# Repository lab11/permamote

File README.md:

Permamote
=========

An energy harvesting sensor mote with backing primary store and a lifetime of ≥10 years.
Permamote monitors temperature, humidity, pressure, light, light color, motion
(both PIR and with an accelerometer) and reports readings over BLE and
802.15.4/Thread.

Hardware
--------
The Permamote hardware is a small, 1 x 2.4 inch rectangular sensor board based
on the Nordic NRF52840 SoC, and the TI BQ25505 for power supply management and
energy harvesting.  Permamote also has an onboard RTC, the AB1815. The board
currently has 6 sensors:

1. Temperature and Humidity (Si7021)
2. Temperature and Pressure (MS5637)
3. Light (MAX44009)
4. Light Color (TCS34725)
5. PIR Motion (EKMB1101111)
6. Accelerometer (LIS2DW12)

The Permamote hardware is located in the [`hardware/permamote`](https://github.com/lab11/permamote/tree/master/hardware/permamote) directory, where you can find
the Eagle design files and case files.

Software
--------
The Permamote uses software located in the
[`software`](https://github.com/lab11/permamote/tree/master/software/).
directory. Follow the directions in the [nrf5x-base
Readme](https://github.com/lab11/nrf5x-base/tree/nrf52832#flash-an-application)
to get your machine set up to build and flash a Permamote.

The primary application is
[`software/apps/permamote_coap`](https://github.com/lab11/permamote/tree/master/software/apps/permamote_coap).
This application samples the
sensors and sends its data to a server running a
[coap-gateway](https://github.com/lab11/gateway/tree/thread/software/coap-gateway-mqtt)
over IP on a [Thread](https://github.com/openthread/openthread) network with a
[border router](https://github.com/openthread/borderrouter).
See the
[tutorial](https://github.com/lab11/permamote/tree/master/tutorial) to set up
your own OpenThread network.

Cloning
-------
To clone both this repository and the required submodules,
clone with the `--recurse-submodules` option:

```
git clone --recurse-submodules git@github.com:lab11/permamote.git
```

Otherwise, you can initialize the submodule and keep submodules up to
date by doing

```
git submodule update --init --recursive
```

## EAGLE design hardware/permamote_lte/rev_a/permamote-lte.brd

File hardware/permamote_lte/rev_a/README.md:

# Notes

## UFL LTE Antenna

Using this one: [Taoglas Limited FXUB65.07.0180C](https://cdn.taoglas.com/datasheets/FXUB65.07.0180C.pdf)

[Digikey here](https://www.digikey.com/product-detail/en/taoglas-limited/FXUB65.07.0180C/931-1455-ND/6362793)

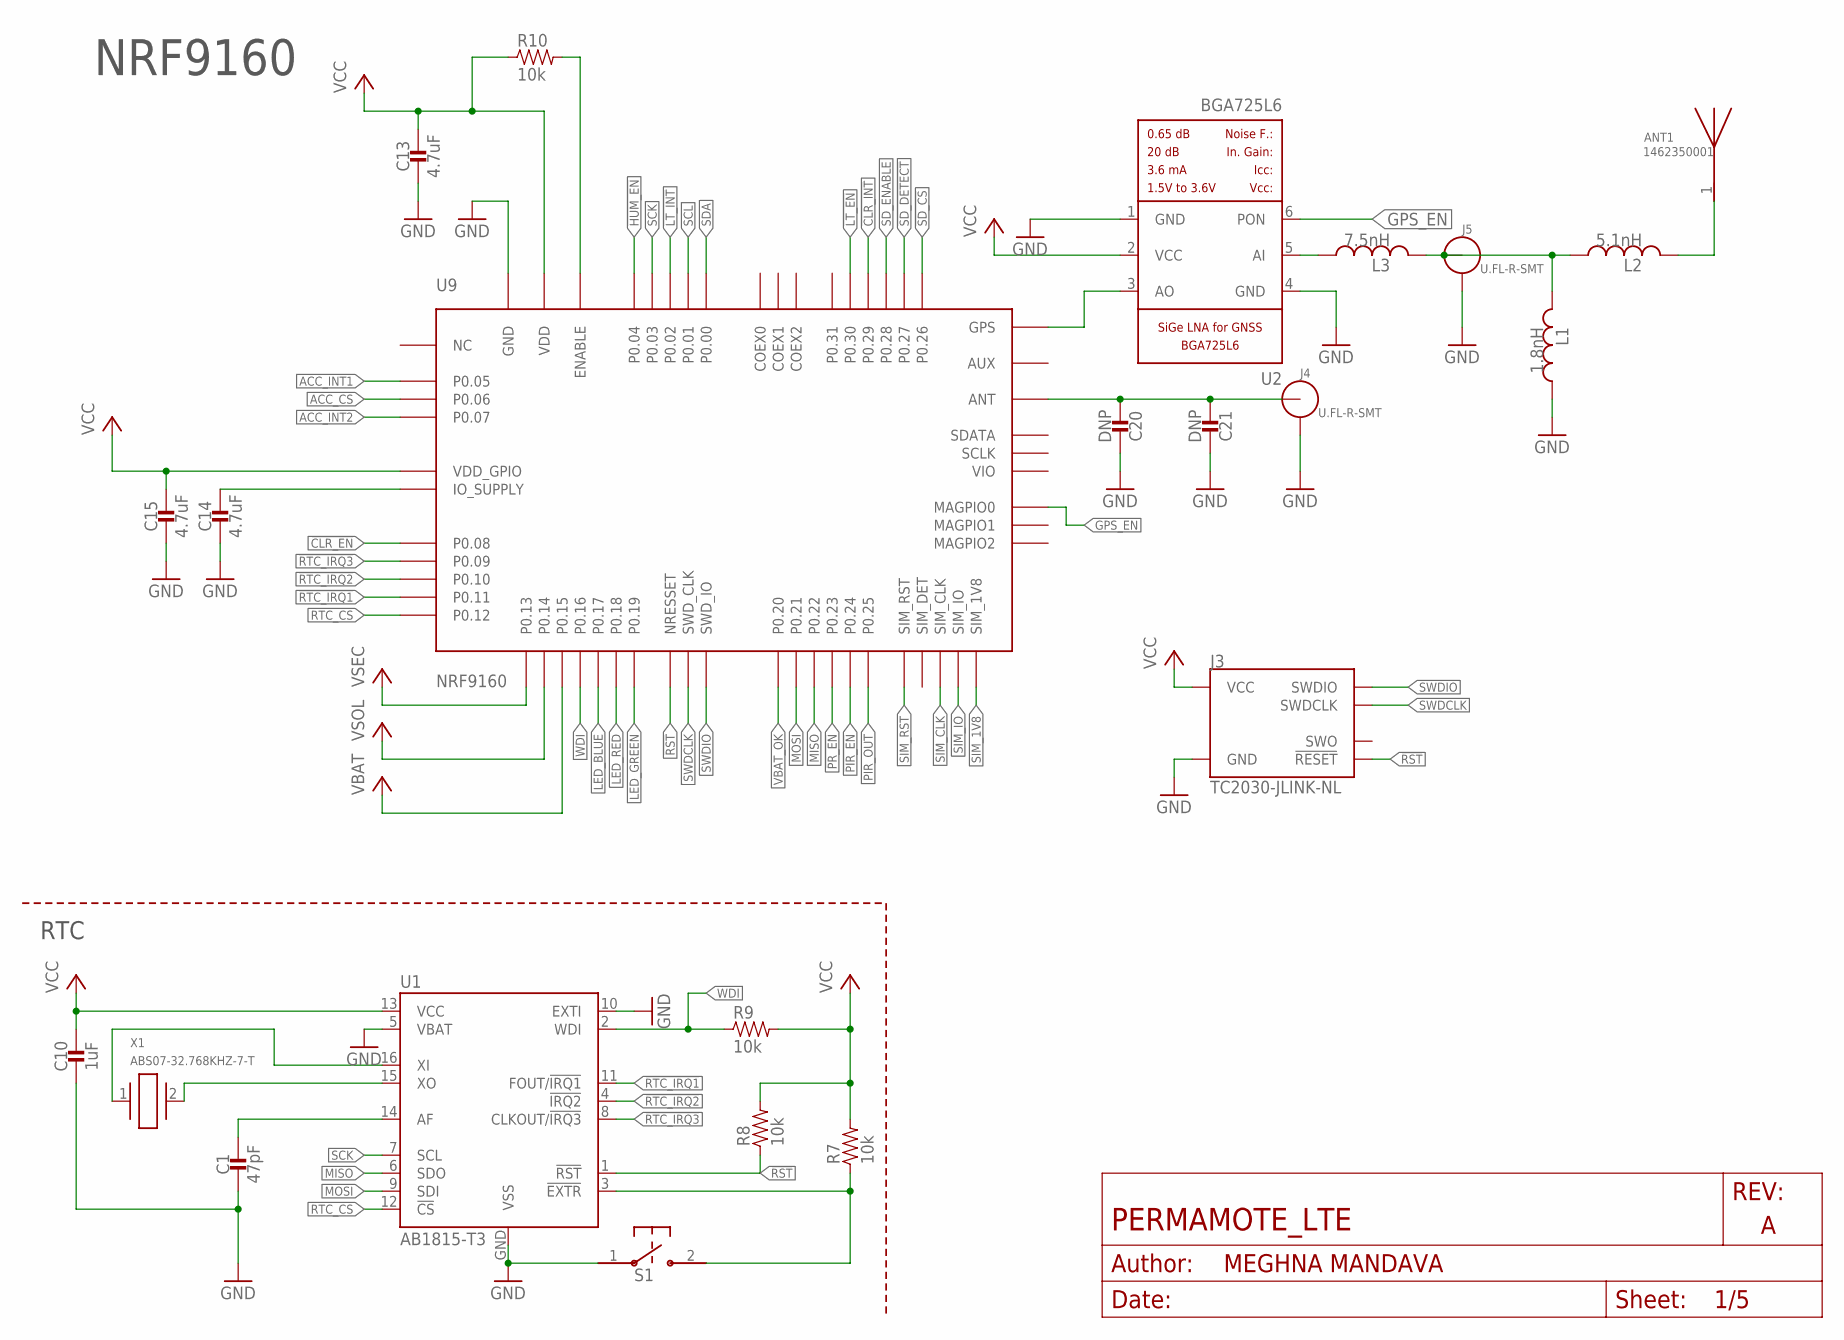
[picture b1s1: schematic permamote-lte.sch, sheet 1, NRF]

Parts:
ANT1: 1462350001; ANT_1462350001; MPN 1462350001; DIGIKEY WM15009CT-ND
C1: 47pF; 0402_CAP; MPN GRM1555C1H470JA01D; DIGIKEY 490-5942-1-ND
C10: 1uF; 0402_CAP; MPN GRM155R70G105KA12D; DIGIKEY 490-7195-1-ND
C13, C14, C15: 4.7uF; 0402_CAP; MPN C1005X5R0J475K050BC; DIGIKEY 445-5947-1-ND
C20, C21: DNP; 0402_CAP
J3: TC2030-JLINK-NL; TC2030-IDC-NL
J4, J5: U.FL-R-SMT; U.FL_SMT
L1: 1.8nH; 0402_CAP; MPN LQG15HS1N8S02D; DIGIKEY 490-2613-1-ND
L2: 5.1nH; 0402_CAP; MPN LQG15HN5N1S02D; DIGIKEY 490-6564-1-ND
L3: 7.5nH; 0402_CAP; MPN LQG15HN7N5J02D; DIGIKEY 490-6565-1-ND
R7, R8, R9, R10: 10k; 0402_RES; MPN RC0402JR-0710KL; DIGIKEY 311-10KJRCT-ND
S1: B3U-1000P
U1: AB1815-T3; QFN-16-3MM
U2: BGA725L6; LNA-TSLP-6-2-ORIG; MPN BGA725L6E6327FTSA1; DIGIKEY BGA725L6E6327FTSA1CT-ND
U9: NRF9160; MPN NRF9160-SICA-R7; DIGIKEY 1490-1076-1-ND
X1: ABS07-32.768KHZ-7-T; 2-SMD

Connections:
!CLR_EN: U9.P0.08; also elsewhere on the board
!CLR_INT: U9.P0.29; also elsewhere on the board
!HUM_EN: U9.P0.04; also elsewhere on the board
!LT_EN: U9.P0.30; also elsewhere on the board
!LT_INT: U9.P0.02; also elsewhere on the board
!PIR_EN: U9.P0.24; also elsewhere on the board
!PR_EN: U9.P0.23; also elsewhere on the board
!RST: J3.3 (!RESET), R8.1, U1.1 (!RST), U9.NRESET (NRESSET); also elsewhere on the board
!RTC_EXTR: R7.1, S1.2, U1.3 (!EXTR)
!RTC_IRQ1: U1.11 (FOUT/!IRQ1), U9.P0.11; also elsewhere on the board
!RTC_IRQ2: U1.4 (!IRQ2), U9.P0.10; also elsewhere on the board
!RTC_IRQ3: U1.8 (CLKOUT/!IRQ3), U9.P0.09; also elsewhere on the board
!SD_CS: U9.P0.26; also elsewhere on the board
!SD_DETECT: U9.P0.27; also elsewhere on the board
ACC_CS: U9.P0.06; also elsewhere on the board
ACC_INT1: U9.P0.05; also elsewhere on the board
ACC_INT2: U9.P0.07; also elsewhere on the board
GND: C1.2, C10.2, C13.2, C14.2, C15.2, C20.1, C21.1, J3.5 (GND), J4.GND1, J4.GND2, J5.GND1, J5.GND2, L1.1, S1.1, U1.5 (VBAT), U1.10 (EXTI), U1.GND (VSS), U2.1 (GND), U2.4 (GND), U9.GND@1 (GND), U9.GND@2 (GND), U9.GND@3 (GND), U9.GND@4 (GND), U9.GND@5 (GND), U9.GND@6 (GND), U9.GND@7 (GND), U9.GND@8 (GND), U9.GND@9 (GND), U9.GND@10 (GND), U9.GND@11 (GND), U9.GND@12 (GND), U9.GND@13 (GND), U9.GND@14 (GND), U9.GND@15 (GND), U9.GND@16 (GND), U9.GND@17 (GND), U9.GND@18 (GND), U9.GND@19 (GND), U9.GND@20 (GND), U9.GND@21 (GND), U9.GND@22 (GND), U9.GND@23 (GND), U9.GND@24 (GND), U9.GND@25 (GND), U9.GND@26 (GND), U9.GND@27 (GND), U9.GND@28 (GND), U9.GND@29 (GND), U9.GND@30 (GND), U9.GND@31 (GND), U9.GND@32 (GND), U9.GND@33 (GND), U9.GND@34 (GND), U9.GND@35 (GND), U9.GND_SHIELD@1 (GND), U9.GND_SHIELD@2 (GND), U9.GND_SHIELD@3 (GND), U9.GND_SHIELD@4 (GND), U9.GND_SHIELD@5 (GND), U9.GND_SHIELD@6 (GND), U9.GND_SHIELD@7 (GND), U9.GND_SHIELD@8 (GND), U9.GND_SHIELD@9 (GND), U9.GND_SHIELD@10 (GND), U9.GND_SHIELD@11 (GND), U9.GND_SHIELD@12 (GND), U9.GND_SHIELD@13 (GND), U9.GND_SHIELD@14 (GND), U9.GND_SHIELD@15 (GND), U9.GND_SHIELD@16 (GND), U9.GND_SHIELD@17 (GND), U9.GND_SHIELD@18 (GND), U9.GND_SHIELD@19 (GND), U9.GND_SHIELD@20 (GND), U9.GND_SHIELD@21 (GND), U9.GND_SHIELD@22 (GND), U9.GND_SHIELD@23 (GND), U9.GND_SHIELD@24 (GND), U9.GND_SHIELD@25 (GND), U9.GND_SHIELD@26 (GND), U9.GND_SHIELD@27 (GND), U9.GND_SHIELD@28 (GND), U9.GND_SHIELD@29 (GND), U9.GND_SHIELD@30 (GND), U9.GND_SHIELD@31 (GND), U9.GND_SHIELD@32 (GND), U9.GND_SHIELD@33 (GND), U9.GND_SHIELD@34 (GND); also elsewhere on the board
GPS_EN: U2.6 (PON), U9.MAGPIO0
LED_BLUE: U9.P0.17; also elsewhere on the board
LED_GREEN: U9.P0.19; also elsewhere on the board
LED_RED: U9.P0.18; also elsewhere on the board
MISO: U1.6 (SDO), U9.P0.22; also elsewhere on the board
MOSI: U1.9 (SDI), U9.P0.21; also elsewhere on the board
unnamed: U2.3 (AO), U9.GPS
unnamed: L3.1, U2.5 (AI)
unnamed: J5.SIG (ANT), L1.2, L2.1, L3.2
unnamed: ANT1.1, L2.2
unnamed: C20.2, C21.2, J4.SIG (ANT), U9.ANT
unnamed: C1.1, U1.14 (AF)
unnamed: R10.2, U9.ENABLE
unnamed: C14.1, U9.IO_SUPPLY
unnamed: U1.15 (XO), X1.2
unnamed: U1.16 (XI), X1.1
PIR_OUT: U9.P0.25; also elsewhere on the board
RTC_CS: U1.12 (!CS), U9.P0.12; also elsewhere on the board
SCK: U1.7 (SCL), U9.P0.03; also elsewhere on the board
SCL: U9.P0.01; also elsewhere on the board
SDA: U9.P0.00; also elsewhere on the board
SD_ENABLE: U9.P0.28; also elsewhere on the board
SIM_1V8: U9.SIM_1V8; also elsewhere on the board
SIM_CLK: U9.SIM_CLK; also elsewhere on the board
SIM_IO: U9.SIM_IO; also elsewhere on the board
SIM_RST: U9.SIM_RST; also elsewhere on the board
SWDCLK: J3.4 (SWDCLK), U9.SWDCLK (SWD_CLK)
SWDIO: J3.2 (SWDIO), U9.SWDIO (SWD_IO)
VBAT: U9.P0.15; also elsewhere on the board
VBAT_OK: U9.P0.20; also elsewhere on the board
VCC: C10.1, C13.1, C15.1, J3.1 (VCC), R7.2, R8.2, R9.2, R10.1, U1.13 (VCC), U2.2 (VCC), U9.VDD@1 (VDD), U9.VDD@2 (VDD), U9.VDD_GPIO; also elsewhere on the board
VSEC: U9.P0.13; also elsewhere on the board
VSOL: U9.P0.14; also elsewhere on the board
WDI: R9.1, U1.2 (WDI), U9.P0.16; also elsewhere on the board

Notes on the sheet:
NRF9160
RTC

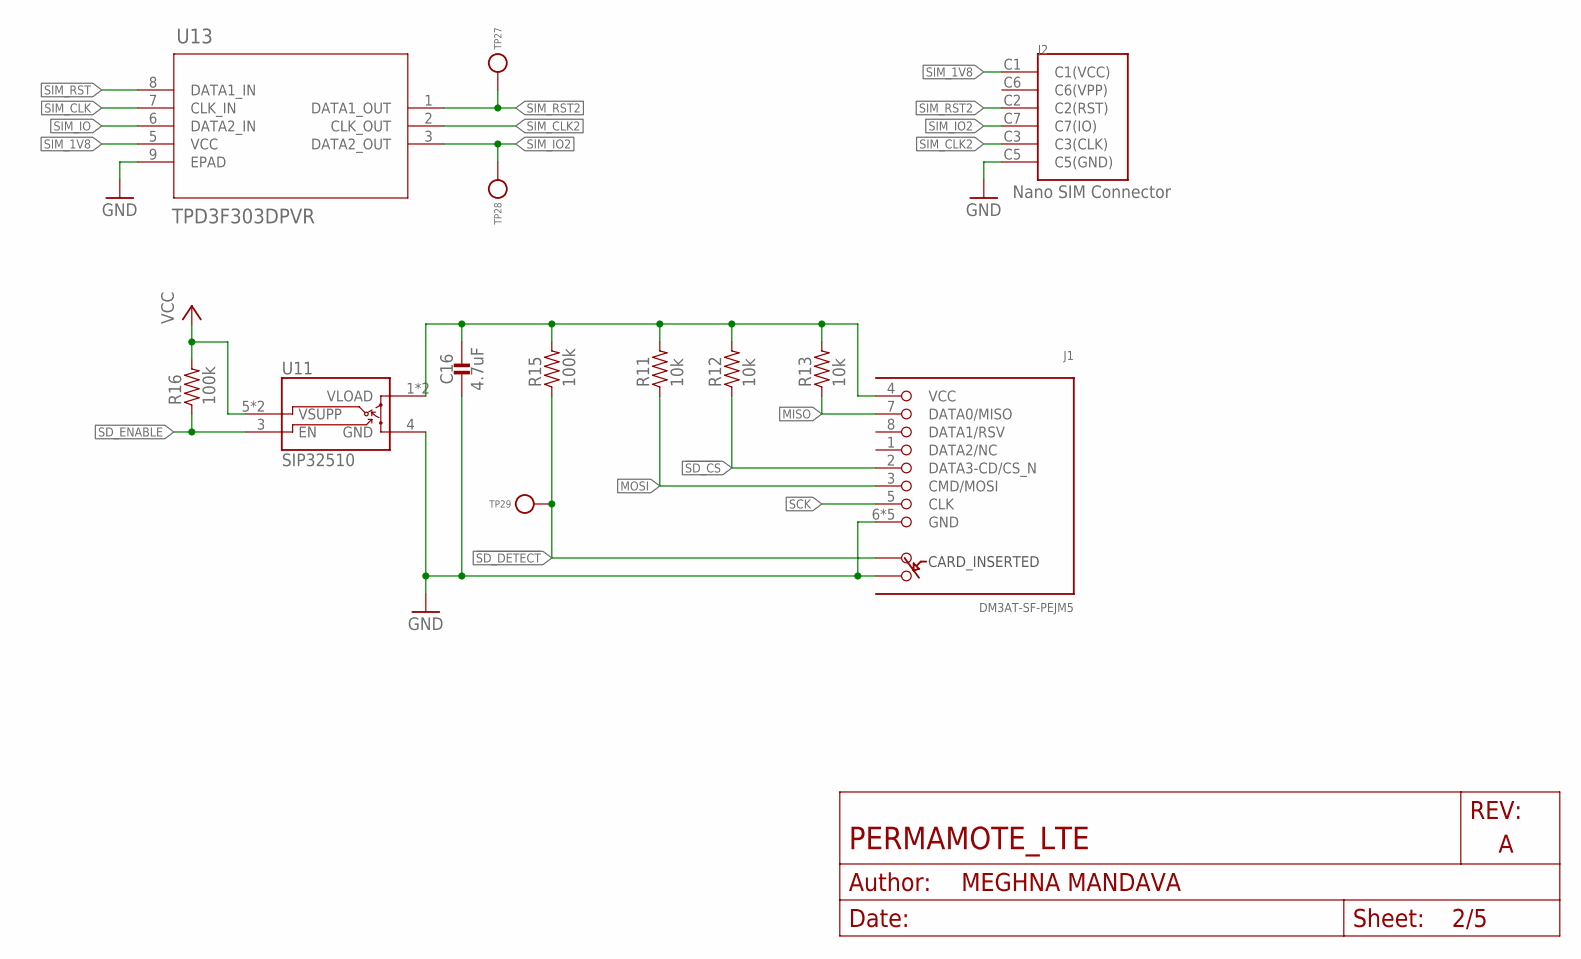
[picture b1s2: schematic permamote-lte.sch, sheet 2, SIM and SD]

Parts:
C16: 4.7uF; 0402_CAP; MPN C1005X5R0J475K050BC; DIGIKEY 445-5947-1-ND
J1: DM3AT-SF-PEJM5
J2: NANO_SIM; WURTH_NANO_SIM
R11, R12, R13: 10k; 0402_RES; MPN RC0402JR-0710KL; DIGIKEY 311-10KJRCT-ND
R15, R16: 100k; 0402_RES; MPN CRCW0402100KFKEDHP; DIGIKEY 541-100KYCT-ND
TP27, TP28, TP29: TEST-POINT; PAD.03X.03
U11: SIP32510; TSOT23-6
U13: TPD3F303DPVR; DPV8_1P7X0P4; MPN TPD3F303DPVR; DIGIKEY 296-28299-1-ND

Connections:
!SD_CS: J1.2 (DATA3-CD/CS_N), R12.1; also elsewhere on the board
!SD_DETECT: J1.A, R15.1, TP29.P$1; also elsewhere on the board
GND: C16.2, J1.6 (GND), J1.B, J1.MOUNT0 (GND), J1.MOUNT1 (GND), J1.MOUNT2 (GND), J1.MOUNT3 (GND), J2.C5 (C5(GND)), U11.4 (GND), U13.9 (EPAD); also elsewhere on the board
MISO: J1.7 (DATA0/MISO), R13.1; also elsewhere on the board
MOSI: J1.3 (CMD/MOSI), R11.1; also elsewhere on the board
unnamed: C16.1, J1.4 (VCC), R11.2, R12.2, R13.2, R15.2, U11.1 (VLOAD), U11.2 (VLOAD)
SCK: J1.5 (CLK); also elsewhere on the board
SD_ENABLE: R16.1, U11.3 (EN); also elsewhere on the board
SIM_1V8: J2.C1 (C1(VCC)), U13.5 (VCC); also elsewhere on the board
SIM_CLK: U13.7 (CLK_IN); also elsewhere on the board
SIM_CLK2: J2.C3 (C3(CLK)), U13.2 (CLK_OUT)
SIM_IO: U13.6 (DATA2_IN); also elsewhere on the board
SIM_IO2: J2.C7 (C7(IO)), TP28.P$1, U13.3 (DATA2_OUT)
SIM_RST: U13.8 (DATA1_IN); also elsewhere on the board
SIM_RST2: J2.C2 (C2(RST)), TP27.P$1, U13.1 (DATA1_OUT)
VCC: R16.2, U11.5 (VSUPP), U11.6 (VSUPP); also elsewhere on the board

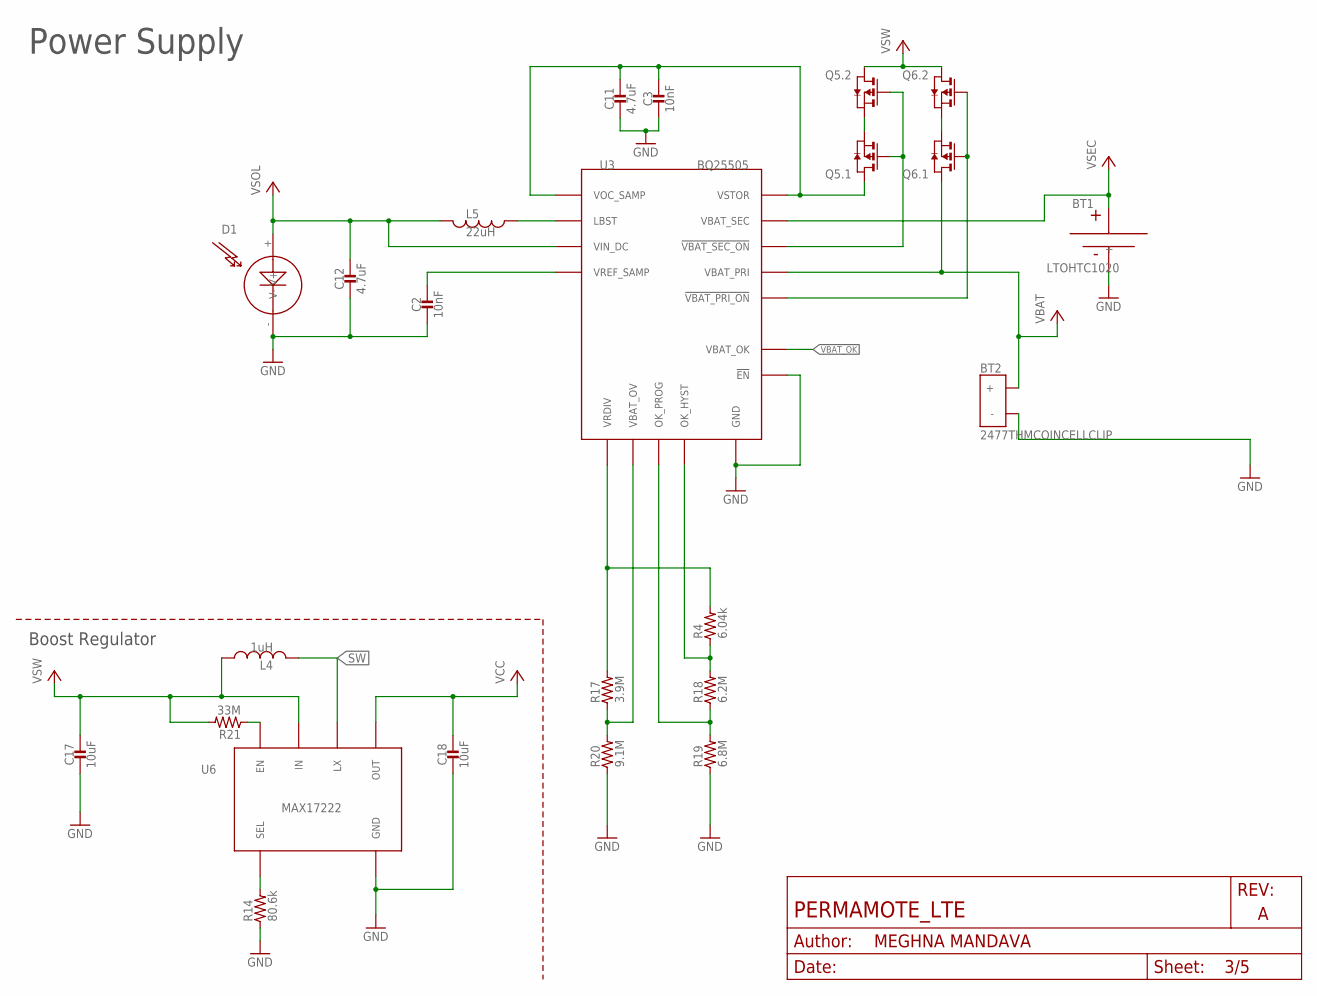
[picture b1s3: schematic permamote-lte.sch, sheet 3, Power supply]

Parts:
BT1: LTOHTC1020; 1020
BT2: 2477THMCOINCELLCLIP; 2477THMCOINCLIP
C2, C3: 10nF; 0402_CAP; MPN GRM155R71H103KA88D; DIGIKEY 490-4516-1-ND
C11, C12: 4.7uF; 0402_CAP; MPN C1005X5R0J475K050BC; DIGIKEY 445-5947-1-ND
C17, C18: 10uF; 0603_CAP; MPN GRM188R60J106ME47D; DIGIKEY 490-3896-1-ND
D1: SOLARCELLHOLES; SOLAR_HOLES
L4: 1uH; IHL-1212BZ-11; MPN IHLP1212BZER1R0M11; DIGIKEY 541-1319-1-ND
L5: 22uH; 74437324220; MPN 74437324220; DIGIKEY 732-3340-1-ND
Q5, Q6: PMDXB950UPEL; XDFN-6
R4: 6.04k; 0402_RES; MPN RC0402FR-076K04L; DIGIKEY YAG2293CT-ND
R14: 80.6k; 0603-RES; MPN RC0603FR-0780K6L; DIGIKEY 311-80.6KHRCT-ND
R17: 3.9M; 0402_RES; MPN RC0402JR-073M9L; DIGIKEY YAG3301CT-ND
R18: 6.2M; 0402_RES; MPN RC0402JR-076M2L; DIGIKEY YAG3309CT-ND
R19: 6.8M; 0402_RES; MPN RC0402JR-076M8L; DIGIKEY YAG3310CT-ND
R20: 9.1M; 0402_RES; MPN RC0402JR-079M1L; DIGIKEY YAG3322CT-ND
R21: 33M; 0603-RES; MPN HMC0603JT33M0; DIGIKEY HMC0603JT33M0CT-ND
U3: BQ25505; S-PVQFN-N20-RGR
U6: MAX17222; UDFN-6-MAXIM

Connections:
!VBAT_PRI_ON: Q6.2 (G), Q6.5 (G), U3.10 (!VBAT_PRI_ON)
!VBAT_SEC_ON: Q5.2 (G), Q5.5 (G), U3.9 (!VBAT_SEC_ON)
GND: BT1.-, BT2.GND (-), C2.2, C3.2, C11.2, C12.2, C17.2, C18.2, D1.- (V-), R14.1, R19.1, R20.1, U3.1 (GND), U3.5 (!EN), U3.6 (GND), U3.15 (GND), U3.16 (GND), U3.17 (GND), U3.PAD (GND), U6.3 (GND); also elsewhere on the board
LBST: L5.P$1 (1), U3.20 (LBST)
unnamed: R14.2, U6.4 (SEL)
unnamed: R21.1, U6.6 (EN)
unnamed: R17.1, R20.2, U3.7 (VBAT_OV)
unnamed: R4.2, R17.2, U3.8 (VRDIV)
unnamed: Q5.1 (S), Q5.4 (S)
unnamed: Q6.1 (S), Q6.4 (S)
unnamed: R18.1, R19.2, U3.12 (OK_PROG)
unnamed: R4.1, R18.2, U3.11 (OK_HYST)
SW: L4.P$2 (2), U6.2 (LX); also elsewhere on the board
VBAT: BT2.1 (+), BT2.2 (+), Q6.6 (D), U3.14 (VBAT_PRI); also elsewhere on the board
VBAT_OK: U3.13 (VBAT_OK); also elsewhere on the board
VCC: C18.1, U6.1 (OUT); also elsewhere on the board
VOC_SAMP_VSTOR: C3.1, C11.1, Q5.6 (D), U3.3 (VOC_SAMP), U3.19 (VSTOR)
VREF_SAMP: C2.1, U3.4 (VREF_SAMP)
VSEC: BT1.+, U3.18 (VBAT_SEC); also elsewhere on the board
VSOL: C12.1, D1.+ (V+), L5.P$2 (2), U3.2 (VIN_DC); also elsewhere on the board
VSW: C17.1, L4.P$1 (1), Q5.3 (D), Q6.3 (D), R21.2, U6.5 (IN)

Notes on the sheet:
Power Supply
Boost Regulator

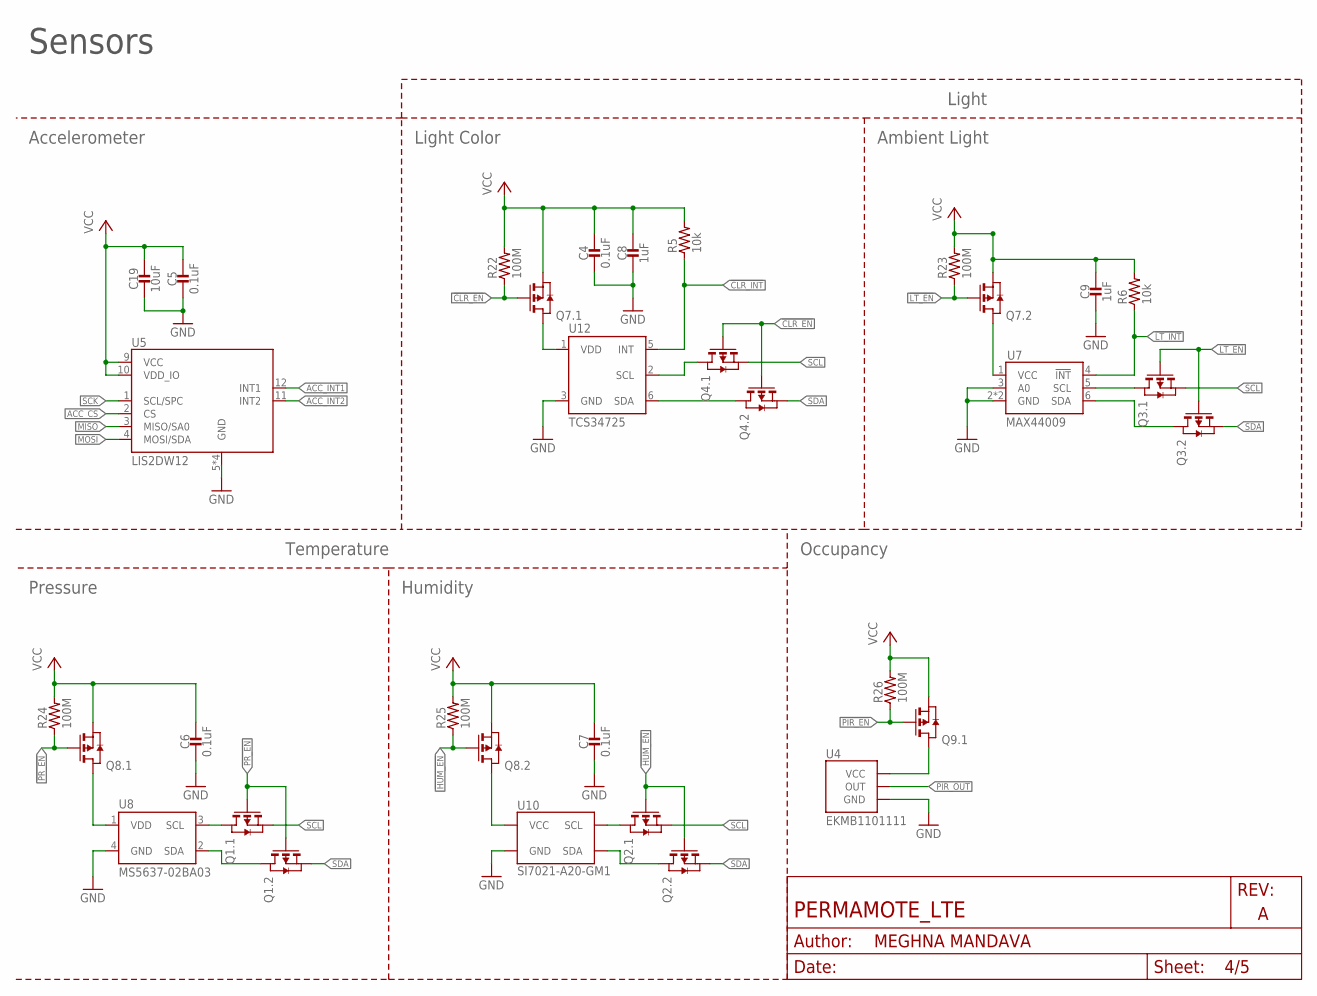
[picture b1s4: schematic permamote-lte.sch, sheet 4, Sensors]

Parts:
C4, C5, C6, C7: 0.1uF; 0402_CAP; MPN GRM155R71C104KA88J; DIGIKEY 490-6328-1-ND
C8, C9: 1uF; 0402_CAP; MPN GRM155R70G105KA12D; DIGIKEY 490-7195-1-ND
C19: 10uF; 0603_CAP; MPN GRM188R60J106ME47D; DIGIKEY 490-3896-1-ND
Q1, Q2, Q3, Q4, Q7, Q8, Q9: PMDXB950UPEL; XDFN-6
R5, R6: 10k; 0402_RES; MPN RC0402JR-0710KL; DIGIKEY 311-10KJRCT-ND
R22, R23, R24, R25, R26: 100M; 0402_RES; MPN HMC0402JT100M; DIGIKEY 541-100MAHCT-ND
U4: EKMB1101111; AMN2
U5: LIS2DW12; LGA-12
U7: MAX44009; UDFN-6-EXPOSED
U8: MS5637-02BA03; 4-SMD
U10: SI7021-A20-GM1; DFN-6/3MM; MPN SI7021-A20-GM1
U12: TCS34725; FN-6

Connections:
!CLR_EN: Q4.2 (G), Q4.5 (G), Q7.2 (G), R22.1; also elsewhere on the board
!CLR_INT: R5.1, U12.5 (INT); also elsewhere on the board
!HUM_EN: Q2.2 (G), Q2.5 (G), Q8.5 (G), R25.1; also elsewhere on the board
!LT_EN: Q3.2 (G), Q3.5 (G), Q7.5 (G), R23.1; also elsewhere on the board
!LT_INT: R6.1, U7.4 (!INT); also elsewhere on the board
!PIR_EN: Q9.2 (G), R26.1; also elsewhere on the board
!PR_EN: Q1.2 (G), Q1.5 (G), Q8.2 (G), R24.1; also elsewhere on the board
ACC_CS: U5.2 (CS); also elsewhere on the board
ACC_INT1: U5.12 (INT1); also elsewhere on the board
ACC_INT2: U5.11 (INT2); also elsewhere on the board
GND: C4.2, C5.2, C6.2, C7.2, C8.2, C9.2, C19.2, U4.GND, U5.5 (GND), U5.6 (GND), U5.7 (GND), U5.8 (GND), U7.2 (GND), U7.3 (A0), U7.EP (GND), U8.4 (GND), U10.2 (GND), U12.3 (GND); also elsewhere on the board
MISO: U5.3 (MISO/SA0); also elsewhere on the board
MOSI: U5.4 (MOSI/SDA); also elsewhere on the board
unnamed: Q7.3 (D), U7.1 (VCC)
unnamed: Q8.6 (D), U8.1 (VDD)
unnamed: Q8.3 (D), U10.5 (VCC)
unnamed: Q9.6 (D), U4.VCC
unnamed: Q7.6 (D), U12.1 (VDD)
unnamed: Q1.6 (D), U8.3 (SCL)
unnamed: Q1.3 (D), U8.2 (SDA)
unnamed: Q2.3 (D), U10.1 (SDA)
unnamed: Q2.6 (D), U10.6 (SCL)
unnamed: Q3.3 (D), U7.6 (SDA)
unnamed: Q3.6 (D), U7.5 (SCL)
unnamed: Q4.3 (D), U12.6 (SDA)
unnamed: Q4.6 (D), U12.2 (SCL)
PIR_OUT: U4.OUT; also elsewhere on the board
SCK: U5.1 (SCL/SPC); also elsewhere on the board
SCL: Q1.1 (S), Q2.1 (S), Q3.1 (S), Q4.1 (S); also elsewhere on the board
SDA: Q1.4 (S), Q2.4 (S), Q3.4 (S), Q4.4 (S); also elsewhere on the board
VCC: C4.1, C5.1, C6.1, C7.1, C8.1, C9.1, C19.1, Q7.1 (S), Q7.4 (S), Q8.1 (S), Q8.4 (S), Q9.1 (S), R5.2, R6.2, R22.2, R23.2, R24.2, R25.2, R26.2, U5.9 (VCC), U5.10 (VDD_IO); also elsewhere on the board

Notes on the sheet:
Sensors
Accelerometer
Temperature
Humidity
Pressure
Ambient Light
Light Color
Light
Occupancy

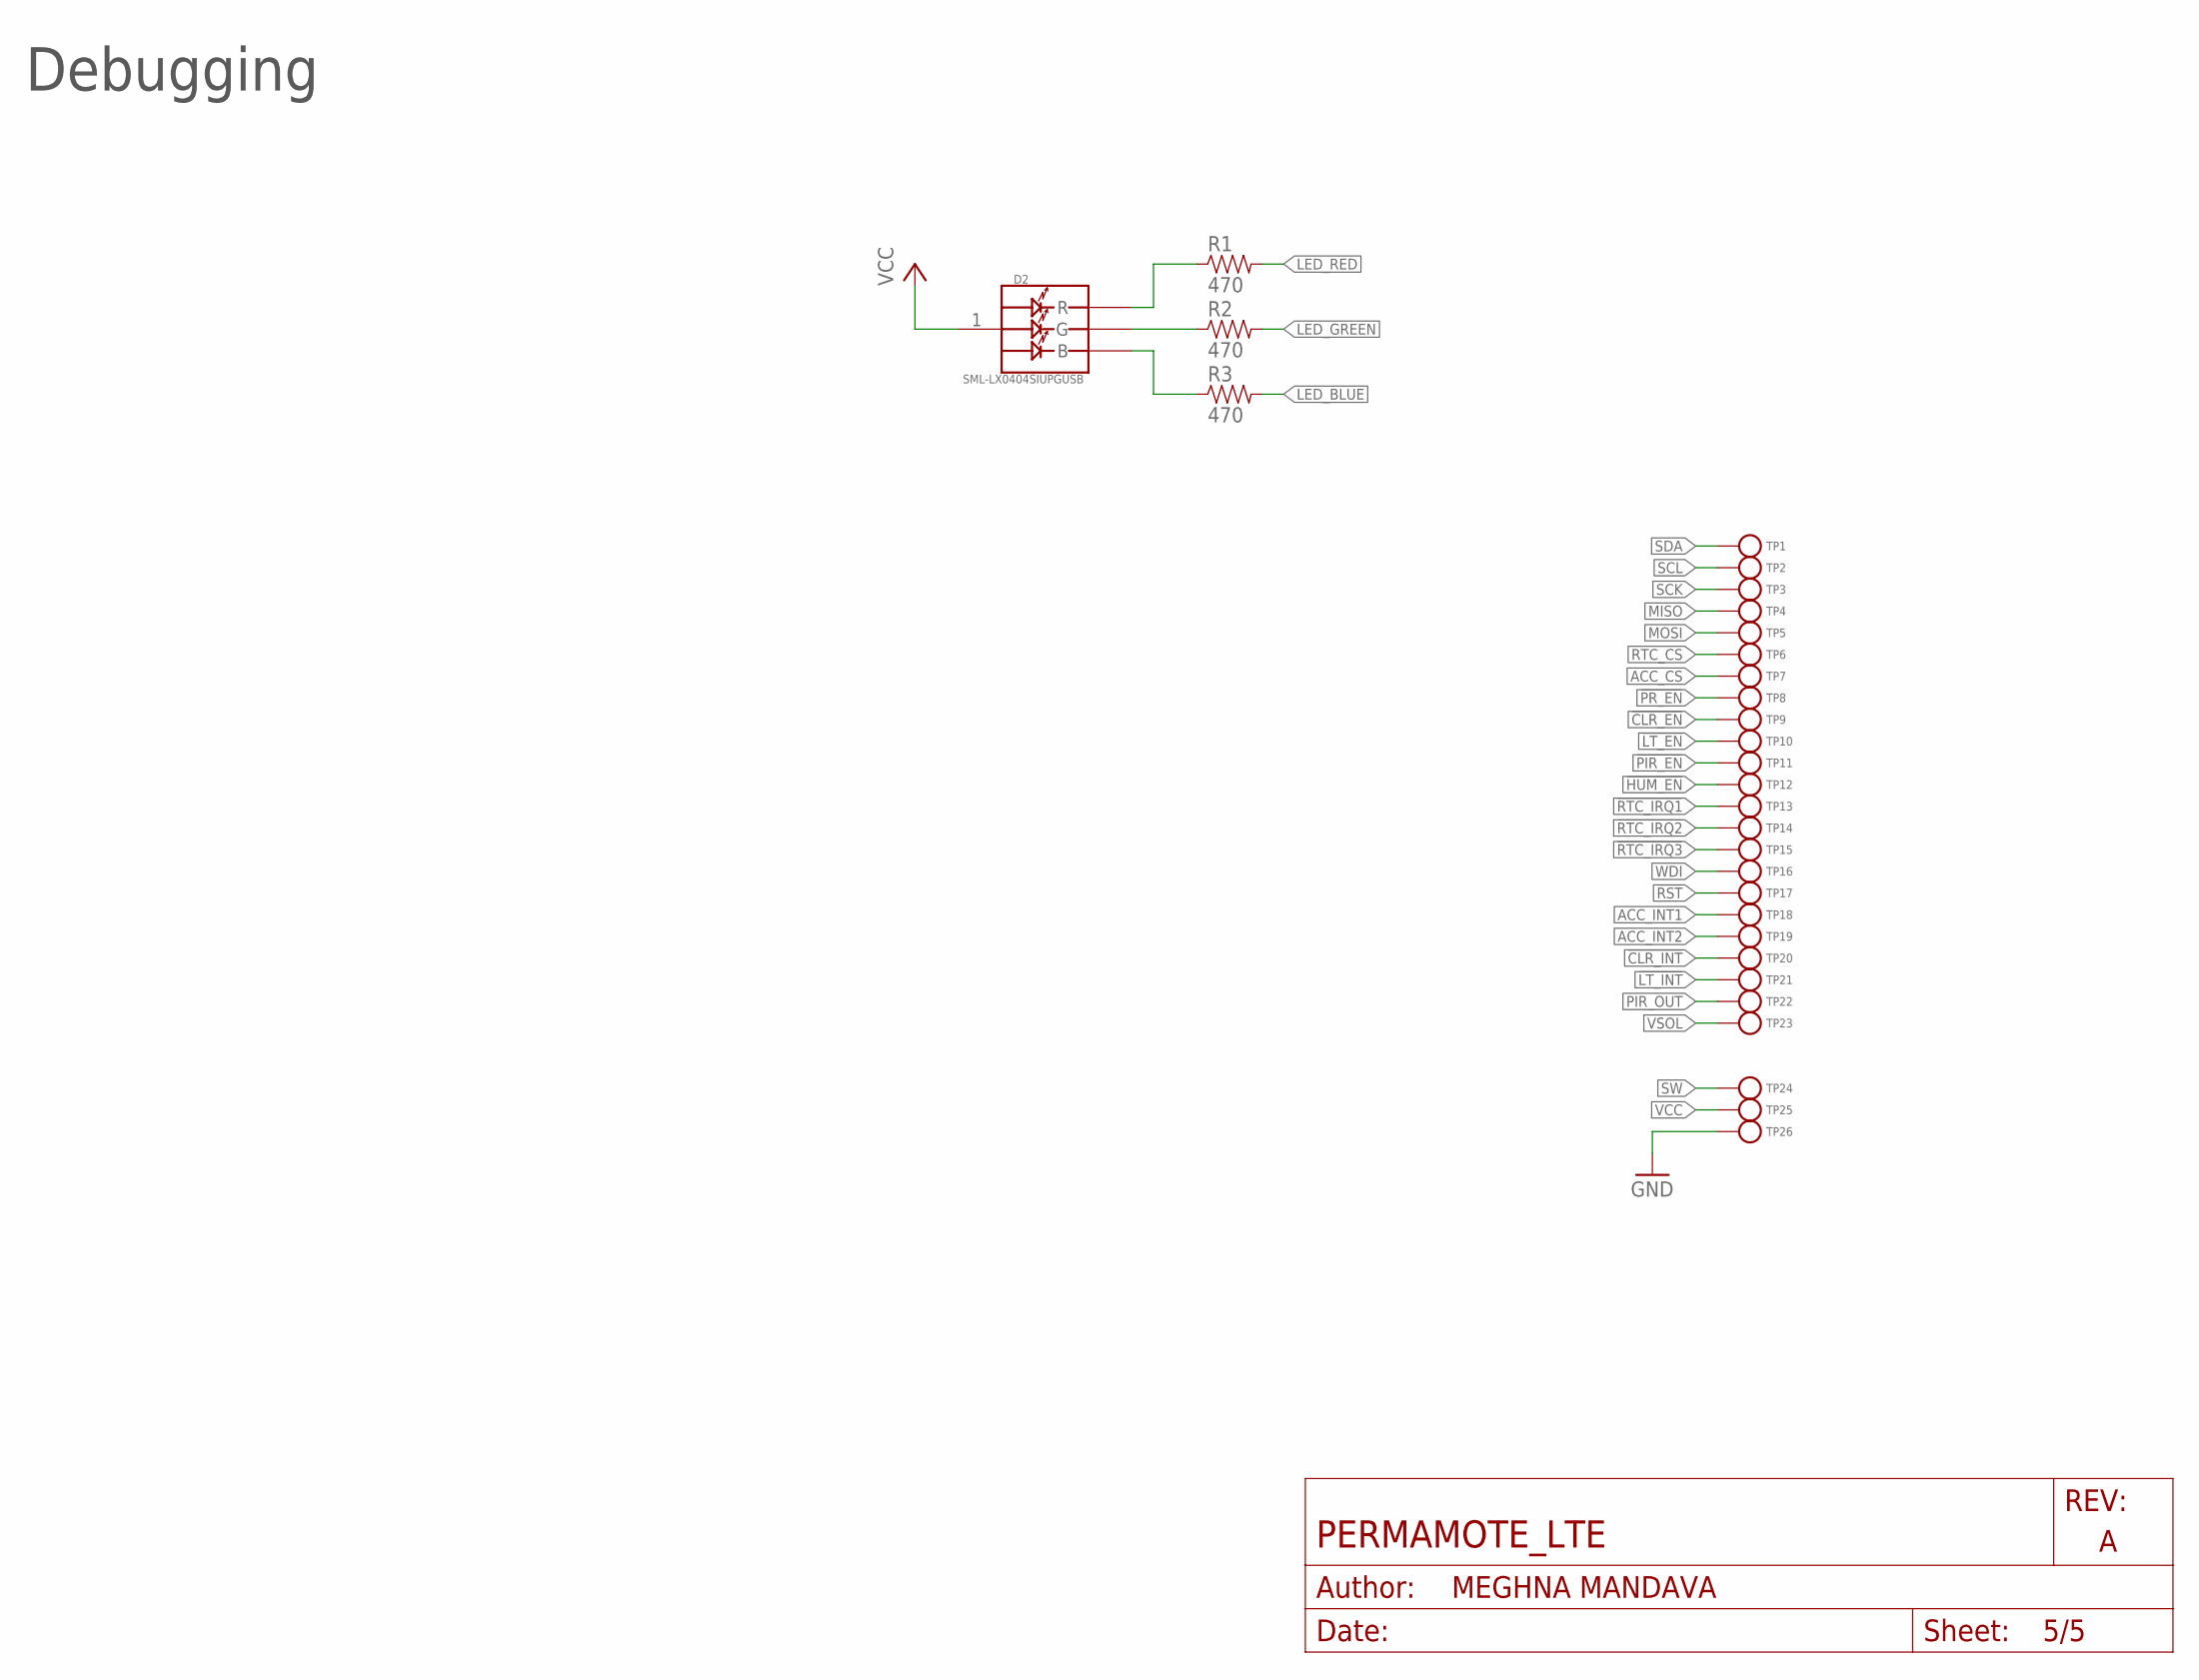
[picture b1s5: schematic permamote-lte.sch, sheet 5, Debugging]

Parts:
D2: SML-LX0404SIUPGUSB; 1MM_SQ_4PAD
R1, R2, R3: 470; 0402_RES; MPN RC0402JR-07470RL; DIGIKEY 311-470JRCT-ND
TP1, TP2, TP3, TP4, TP5, TP6, TP7, TP8, TP9, TP10, TP11, TP12, TP13, TP14, TP15, TP16, TP17, TP18, TP19, TP20, TP21, TP22, TP23, TP24, TP25, TP26: TEST-POINT; PAD.03X.03

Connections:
!CLR_EN: TP9.P$1; also elsewhere on the board
!CLR_INT: TP20.P$1; also elsewhere on the board
!HUM_EN: TP12.P$1; also elsewhere on the board
!LT_EN: TP10.P$1; also elsewhere on the board
!LT_INT: TP21.P$1; also elsewhere on the board
!PIR_EN: TP11.P$1; also elsewhere on the board
!PR_EN: TP8.P$1; also elsewhere on the board
!RST: TP17.P$1; also elsewhere on the board
!RTC_IRQ1: TP13.P$1; also elsewhere on the board
!RTC_IRQ2: TP14.P$1; also elsewhere on the board
!RTC_IRQ3: TP15.P$1; also elsewhere on the board
ACC_CS: TP7.P$1; also elsewhere on the board
ACC_INT1: TP18.P$1; also elsewhere on the board
ACC_INT2: TP19.P$1; also elsewhere on the board
GND: TP26.P$1; also elsewhere on the board
LED_BLUE: R3.2; also elsewhere on the board
LED_GREEN: R2.2; also elsewhere on the board
LED_RED: R1.2; also elsewhere on the board
MISO: TP4.P$1; also elsewhere on the board
MOSI: TP5.P$1; also elsewhere on the board
unnamed: D2.2 (R), R1.1
unnamed: D2.4 (G), R2.1
unnamed: D2.3 (B), R3.1
PIR_OUT: TP22.P$1; also elsewhere on the board
RTC_CS: TP6.P$1; also elsewhere on the board
SCK: TP3.P$1; also elsewhere on the board
SCL: TP2.P$1; also elsewhere on the board
SDA: TP1.P$1; also elsewhere on the board
SW: TP24.P$1; also elsewhere on the board
VCC: D2.1 (VDD), TP25.P$1; also elsewhere on the board
VSOL: TP23.P$1; also elsewhere on the board
WDI: TP16.P$1; also elsewhere on the board

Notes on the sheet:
Debugging

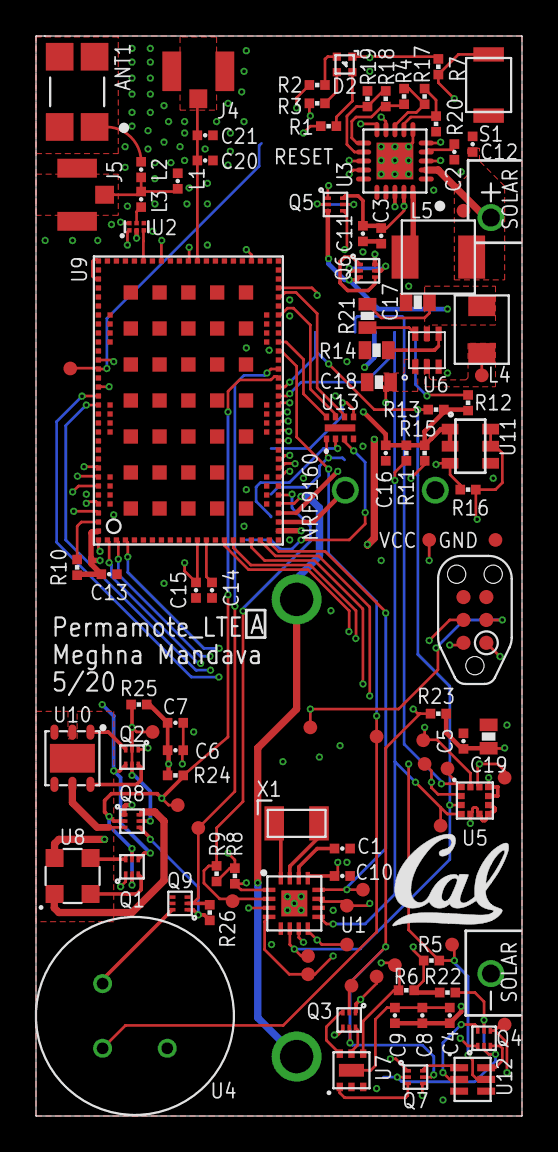
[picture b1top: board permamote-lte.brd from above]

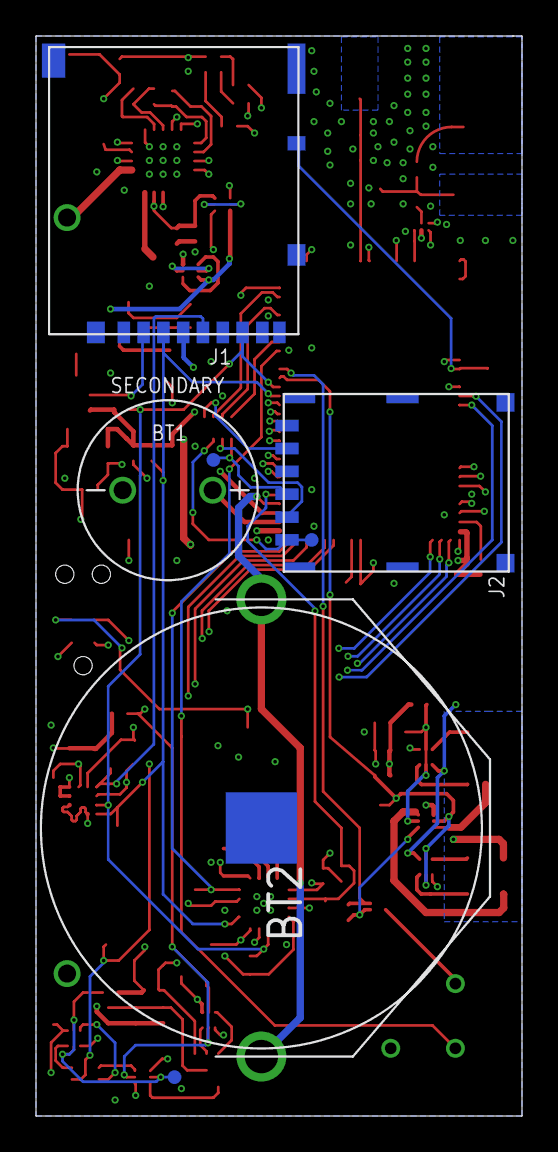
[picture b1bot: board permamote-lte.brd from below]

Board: 4 copper layers, 27.0 x 60.0 mm, 116 parts (7 on the bottom side), 87 nets.

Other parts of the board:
U$2: UCB_CAL_200MIL

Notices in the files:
parts and their libraries:
SparkFun-Connectors: Licensing: CC v3.0 Share-Alike You are welcome to use this library for commercial purposes.
